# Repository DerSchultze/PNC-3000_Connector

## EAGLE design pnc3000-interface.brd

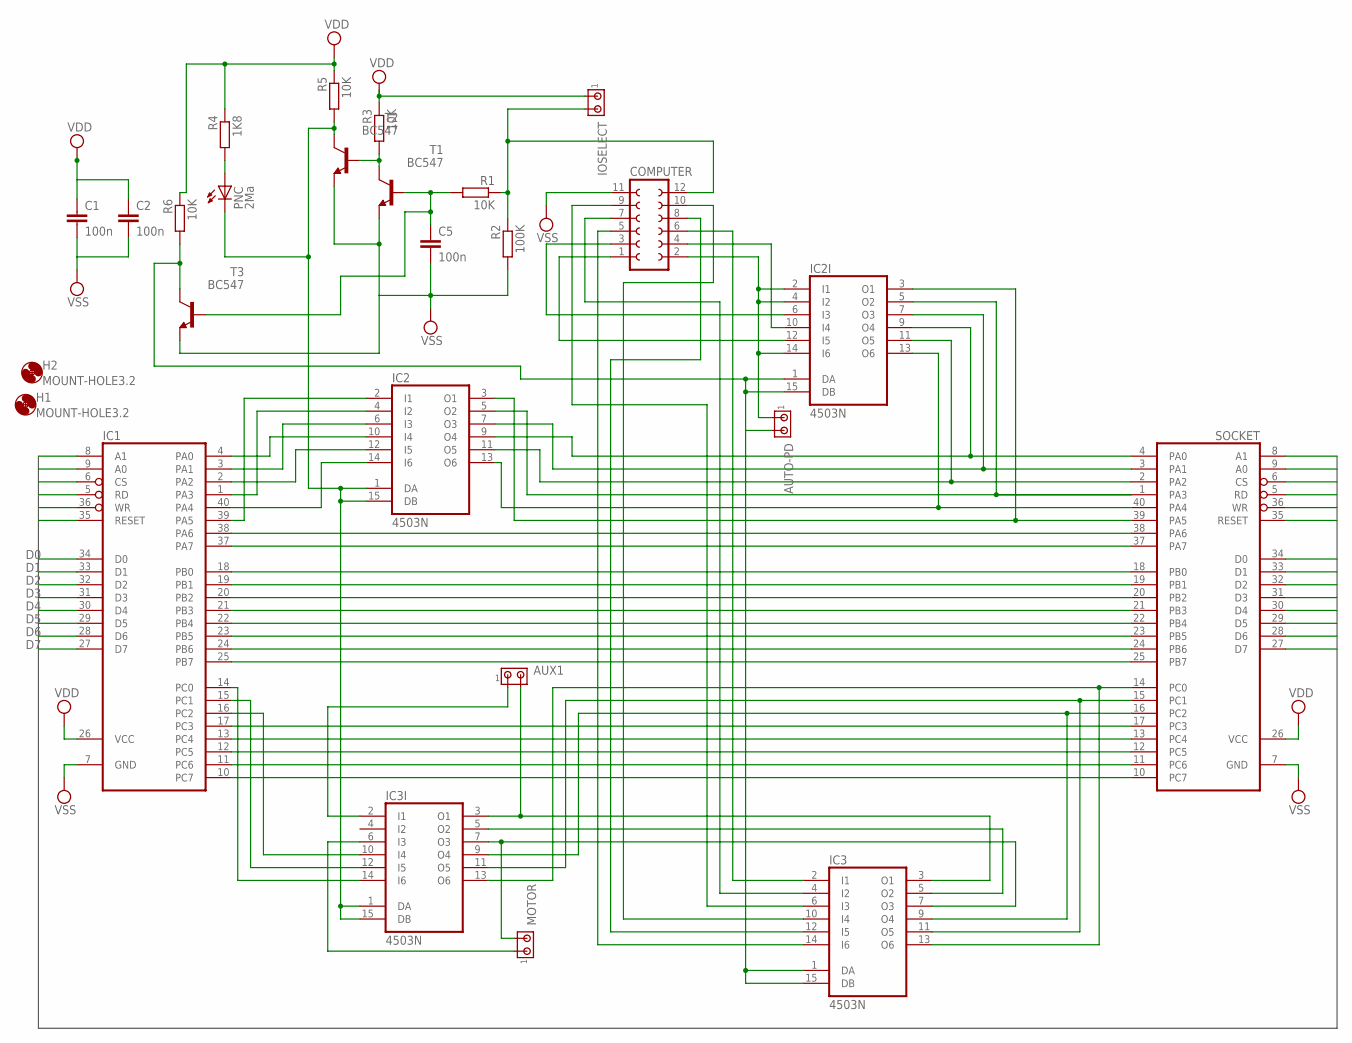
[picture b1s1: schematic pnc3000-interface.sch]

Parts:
AUTO-PD: MTA02-100; 10X02MTA
AUX1: MTA02-100; 10X02MTA
C1, C2, C5: 100n; C050-024X044
COMPUTER: FE06-2W
H1, H2: MOUNT-HOLE3.2; 3,2
IC1: 82C55A; DIL40
IC2, IC2I, IC3, IC3I: 4503N; DIL16
IOSELECT: MTA02-100; 10X02MTA
MOTOR: MTA02-100; 10X02MTA
PNC: 2Ma; LED5MM
R1, R3, R5, R6: 10K; 0207/10
R2: 100K; 0207/10
R4: 1K8; 0207/10
SOCKET: 82C55A; DIL40
T1, T2, T3: BC547; TO92

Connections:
A0: IC1.9 (A0), SOCKET.9 (A0)
A1: IC1.8 (A1), SOCKET.8 (A1)
CS: IC1.6 (CS), SOCKET.6 (CS)
D0: IC1.34 (D0), SOCKET.34 (D0)
D1: IC1.33 (D1), SOCKET.33 (D1)
D2: IC1.32 (D2), SOCKET.32 (D2)
D3: IC1.31 (D3), SOCKET.31 (D3)
D4: IC1.30 (D4), SOCKET.30 (D4)
D5: IC1.29 (D5), SOCKET.29 (D5)
D6: IC1.28 (D6), SOCKET.28 (D6)
D7: IC1.27 (D7), SOCKET.27 (D7)
EXT-ENABLE: AUTO-PD.2, IC2I.1 (DA), IC2I.15 (DB), IC3.1 (DA), IC3.15 (DB), R6.2, T3.3 (C)
MOTOR: IC3I.6 (I3), MOTOR.1
unnamed: IC1.18 (PB0), SOCKET.18 (PB0)
unnamed: IC1.19 (PB1), SOCKET.19 (PB1)
unnamed: IC1.20 (PB2), SOCKET.20 (PB2)
unnamed: IC1.21 (PB3), SOCKET.21 (PB3)
unnamed: IC1.22 (PB4), SOCKET.22 (PB4)
unnamed: IC1.23 (PB5), SOCKET.23 (PB5)
unnamed: IC1.24 (PB6), SOCKET.24 (PB6)
unnamed: IC1.25 (PB7), SOCKET.25 (PB7)
unnamed: IC1.11 (PC6), SOCKET.11 (PC6)
unnamed: IC1.10 (PC7), SOCKET.10 (PC7)
unnamed: IC1.37 (PA7), SOCKET.37 (PA7)
unnamed: IC1.17 (PC3), SOCKET.17 (PC3)
unnamed: IC1.13 (PC4), SOCKET.13 (PC4)
unnamed: IC1.12 (PC5), SOCKET.12 (PC5)
unnamed: IC1.38 (PA6), SOCKET.38 (PA6)
unnamed: IC1.4 (PA0), IC2.10 (I4)
unnamed: IC2.9 (O4), IC2I.9 (O4), SOCKET.4 (PA0)
unnamed: IC1.3 (PA1), IC2.6 (I3)
unnamed: IC2.7 (O3), IC2I.7 (O3), SOCKET.3 (PA1)
unnamed: IC1.2 (PA2), IC2.12 (I5)
unnamed: IC2.11 (O5), IC2I.11 (O5), SOCKET.2 (PA2)
unnamed: IC1.1 (PA3), IC2.4 (I2)
unnamed: IC2.5 (O2), IC2I.5 (O2), SOCKET.1 (PA3)
unnamed: IC1.39 (PA5), IC2.2 (I1)
unnamed: IC2.3 (O1), IC2I.3 (O1), SOCKET.39 (PA5)
unnamed: IC1.40 (PA4), IC2.14 (I6)
unnamed: IC2.13 (O6), IC2I.13 (O6), SOCKET.40 (PA4)
unnamed: IC1.16 (PC2), IC3I.10 (I4)
unnamed: IC3.9 (O4), IC3I.9 (O4), SOCKET.16 (PC2)
unnamed: IC1.15 (PC1), IC3I.12 (I5)
unnamed: IC3.11 (O5), IC3I.11 (O5), SOCKET.15 (PC1)
unnamed: IC1.14 (PC0), IC3I.14 (I6)
unnamed: IC3.13 (O6), IC3I.13 (O6), SOCKET.14 (PC0)
unnamed: COMPUTER.6, IC3.2 (I1)
unnamed: COMPUTER.5, IC3.14 (I6)
unnamed: COMPUTER.7, IC3.4 (I2)
unnamed: COMPUTER.1, IC2I.12 (I5)
unnamed: COMPUTER.3, IC2I.6 (I3)
unnamed: COMPUTER.4, IC2I.10 (I4)
unnamed: AUTO-PD.1, COMPUTER.2, IC2I.2 (I1), IC2I.4 (I2), IC2I.14 (I6)
unnamed: COMPUTER.8, IC3.12 (I5)
unnamed: COMPUTER.9, IC3.6 (I3)
unnamed: COMPUTER.10, IC3.10 (I4)
unnamed: IC3.7 (O3), IC3I.7 (O3), MOTOR.2
unnamed: IC3.5 (O2), IC3I.5 (O2)
unnamed: AUX1.2, IC3.3 (O1), IC3I.3 (O1)
unnamed: PNC.A, R4.2
unnamed: COMPUTER.12, IOSELECT.2, R1.1, R2.1
unnamed: C5.1, R1.2, T1.2 (B), T3.2 (B)
unnamed: AUX1.1, IC3I.2 (I1)
unnamed: R3.2, T1.3 (C), T2.2 (B)
PNC-ENABLE: IC2.1 (DA), IC2.15 (DB), IC3I.1 (DA), IC3I.15 (DB), PNC.K (C), R5.2, T2.3 (C)
RD: IC1.5 (RD), SOCKET.5 (RD)
RESET: IC1.35 (RESET), SOCKET.35 (RESET)
VDD: C1.1, C2.1, IC1.26 (VCC), IC2.16 (VDD), IC2I.16 (VDD), IC3.16 (VDD), IC3I.16 (VDD), IOSELECT.1, R3.1, R4.1, R5.1, R6.1, SOCKET.26 (VCC)
VSS: C1.2, C2.2, C5.2, COMPUTER.11, IC1.7 (GND), IC2.8 (VSS), IC2I.8 (VSS), IC3.8 (VSS), IC3I.8 (VSS), R2.2, SOCKET.7 (GND), T1.1 (E), T2.1 (E), T3.1 (E)
WR: IC1.36 (WR), SOCKET.36 (WR)

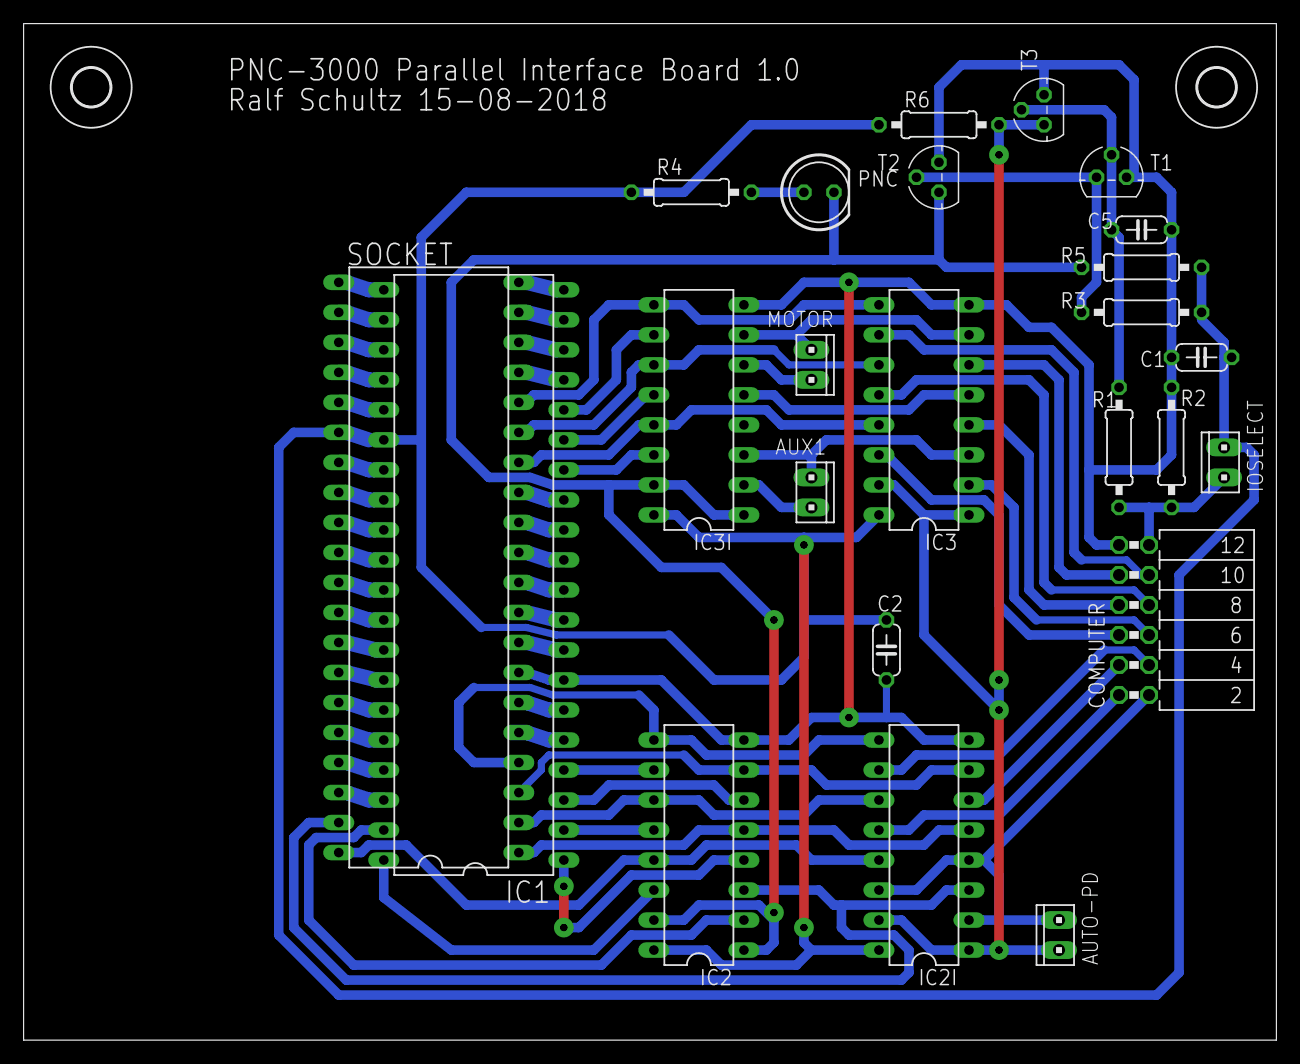
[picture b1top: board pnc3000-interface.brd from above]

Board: 2 copper layers, 106.0 x 86.0 mm, 26 parts (0 on the bottom side), 70 nets.

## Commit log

2020-06-17 Add g-code
